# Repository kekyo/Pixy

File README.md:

# Pixy - Single board computer projects

Moved to [GitLab](https://gitlab.com/kekyo/Pixy).

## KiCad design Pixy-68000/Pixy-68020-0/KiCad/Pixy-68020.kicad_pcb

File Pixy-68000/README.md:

# Pixy-68000

## Specification

* [Motorola (NXP Freescale semiconductor) MC68SEC000-20](https://www.nxp.com/docs/en/product-brief/MC68SEC000.pdf) (Static low-powered m68k arch.)
* [ATMEL AVR ATMega-328PB](https://www.microchip.com/en-us/product/atmega328p)
  * Co-processor for 7segLEDs, LEDs, switches and serial interface.
  * Can program Arduino-like with [MiniCore project](https://github.com/MCUdude/MiniCore)
  * It can also be used in "ATMega-328P".
* [LATTICE MachXO2 LCMXO2-640](https://www.latticesemi.com/products/fpgaandcpld/machxo2)
  * Bus controller, captured all signals from the CPU.
* SRAM 1MB (512kbit * 2)
* Flash PROM 1MB (512kbit * 2, PLCC)

## PCB (Pixy-68000-0)

## Schematic (Pixy-68000-0)

[Pixy-68000-0-sch (PDF)](Images/Pixy-68000-0-sch.pdf)

## Errata (Pixy-68000-0)

1. Will fail writing Arduino (MiniCore) bootloader at first time.
   Please make this connection in your hand instead of J2 `AVR_ISP` connector.
   Then write to use Arduino MiniCore firmware writer.
   Once the firmware is written, this quick-hack wiring is not required thereafter.

## TODO:

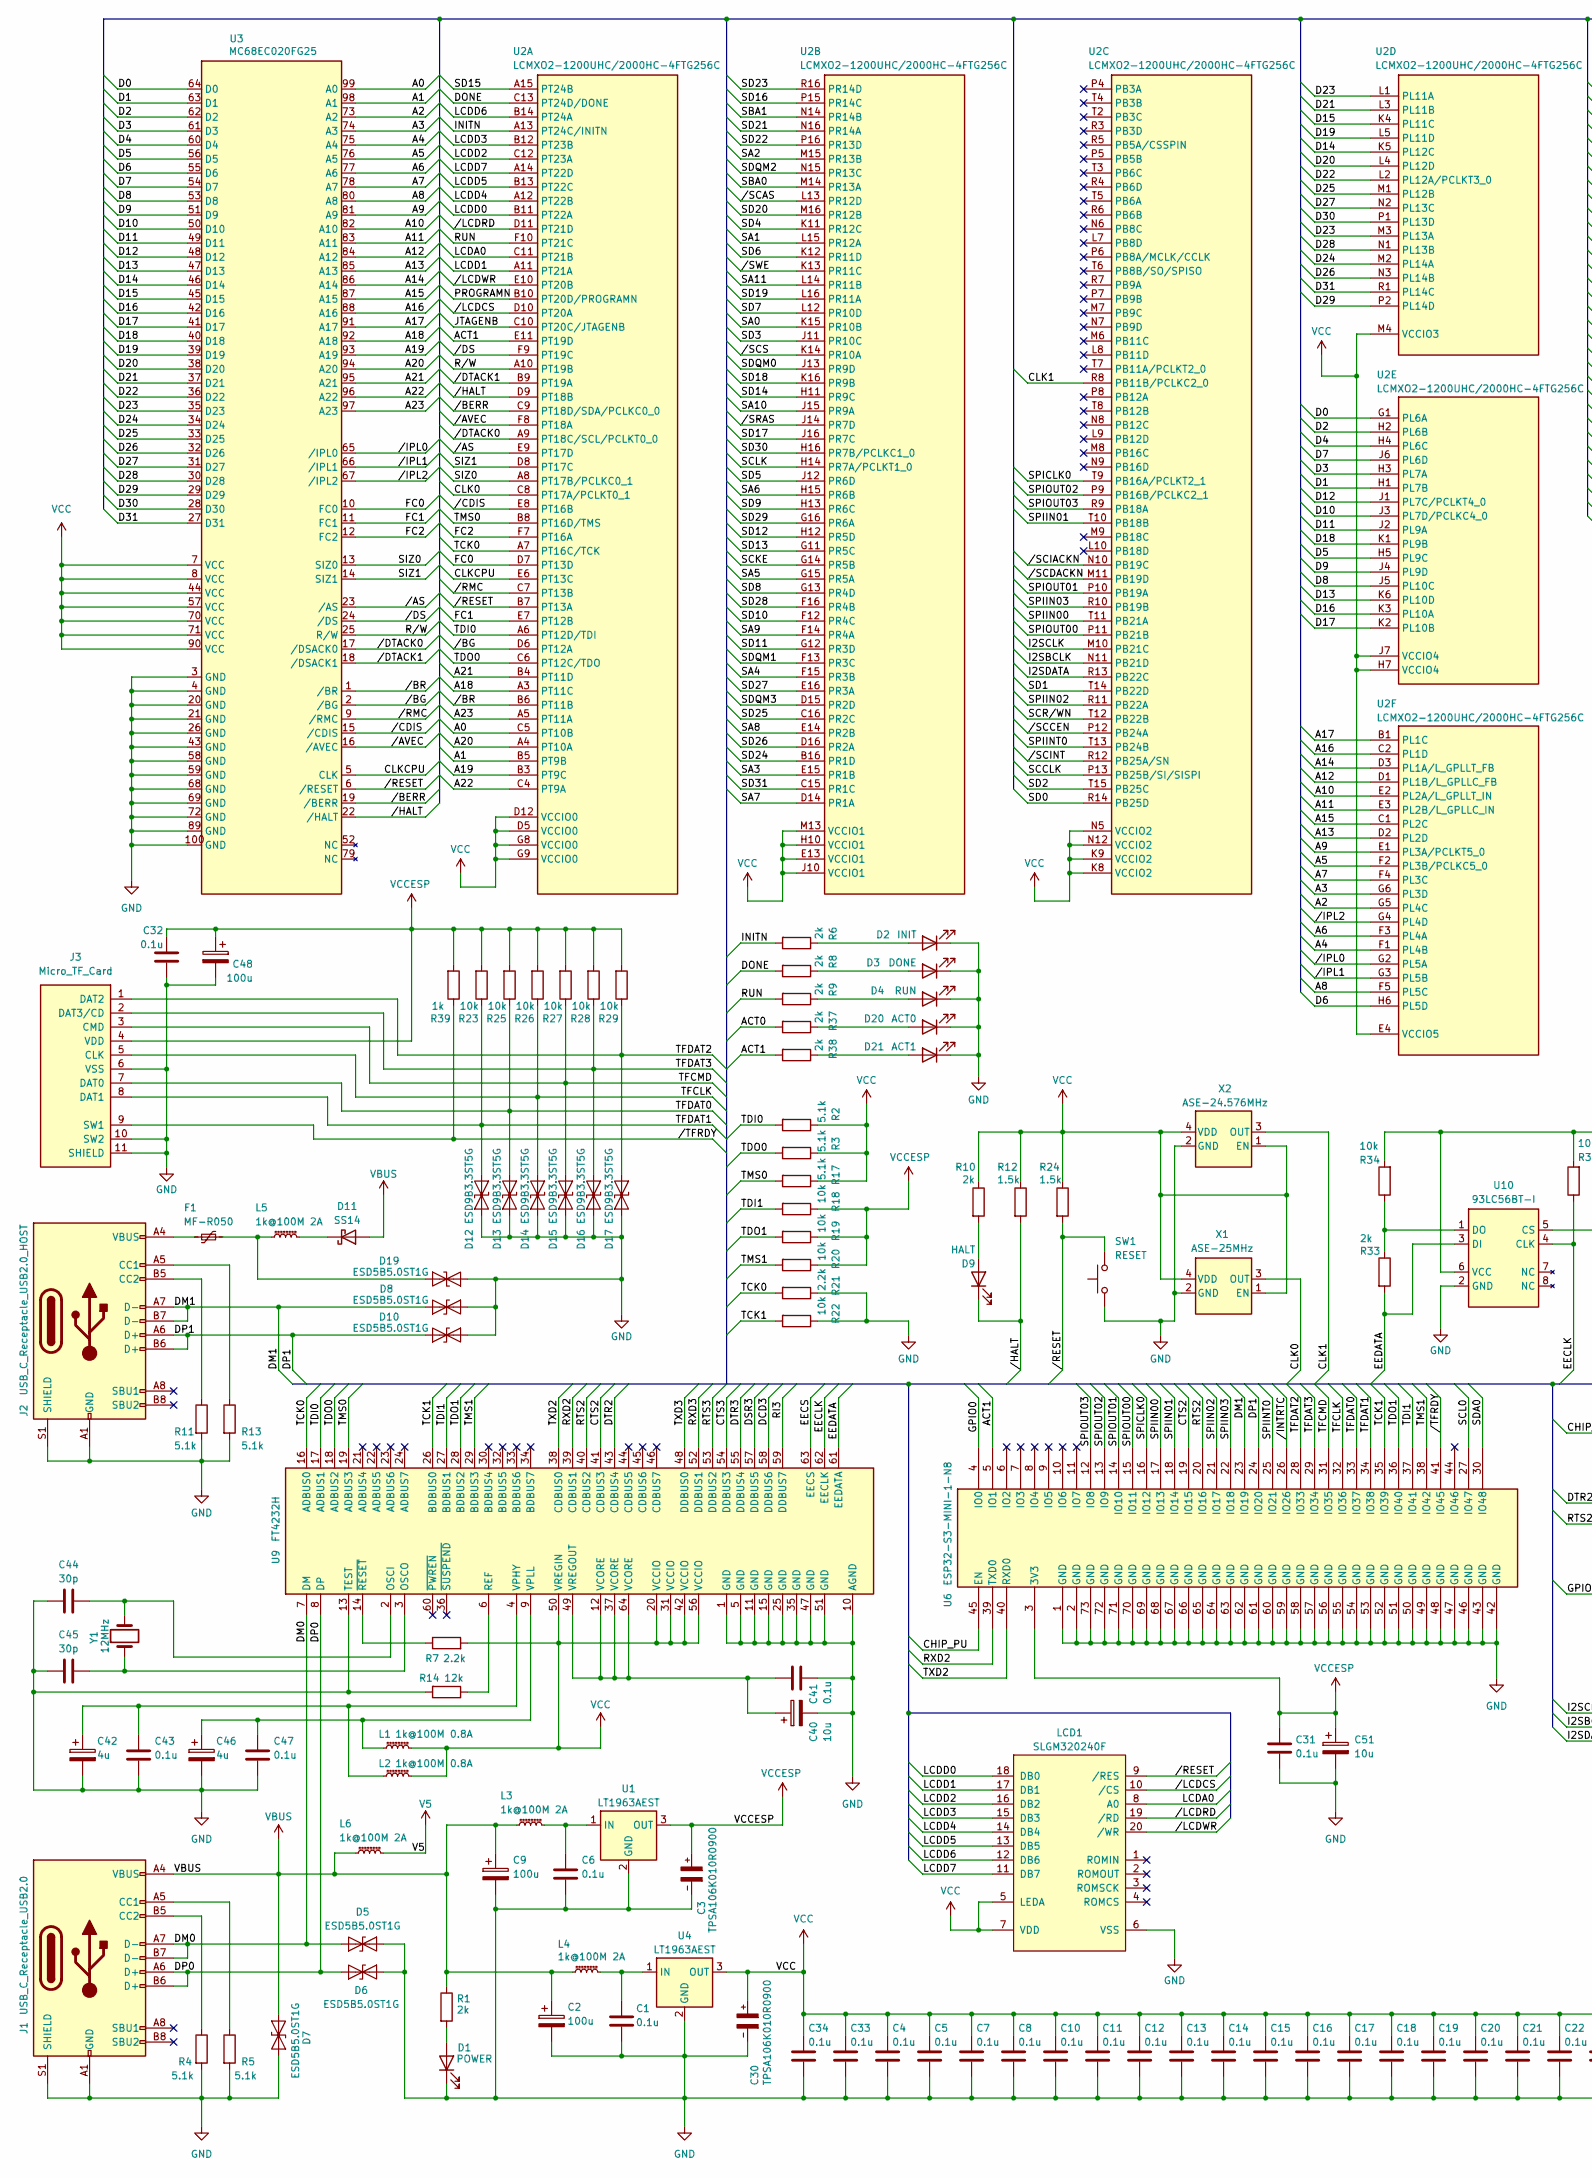
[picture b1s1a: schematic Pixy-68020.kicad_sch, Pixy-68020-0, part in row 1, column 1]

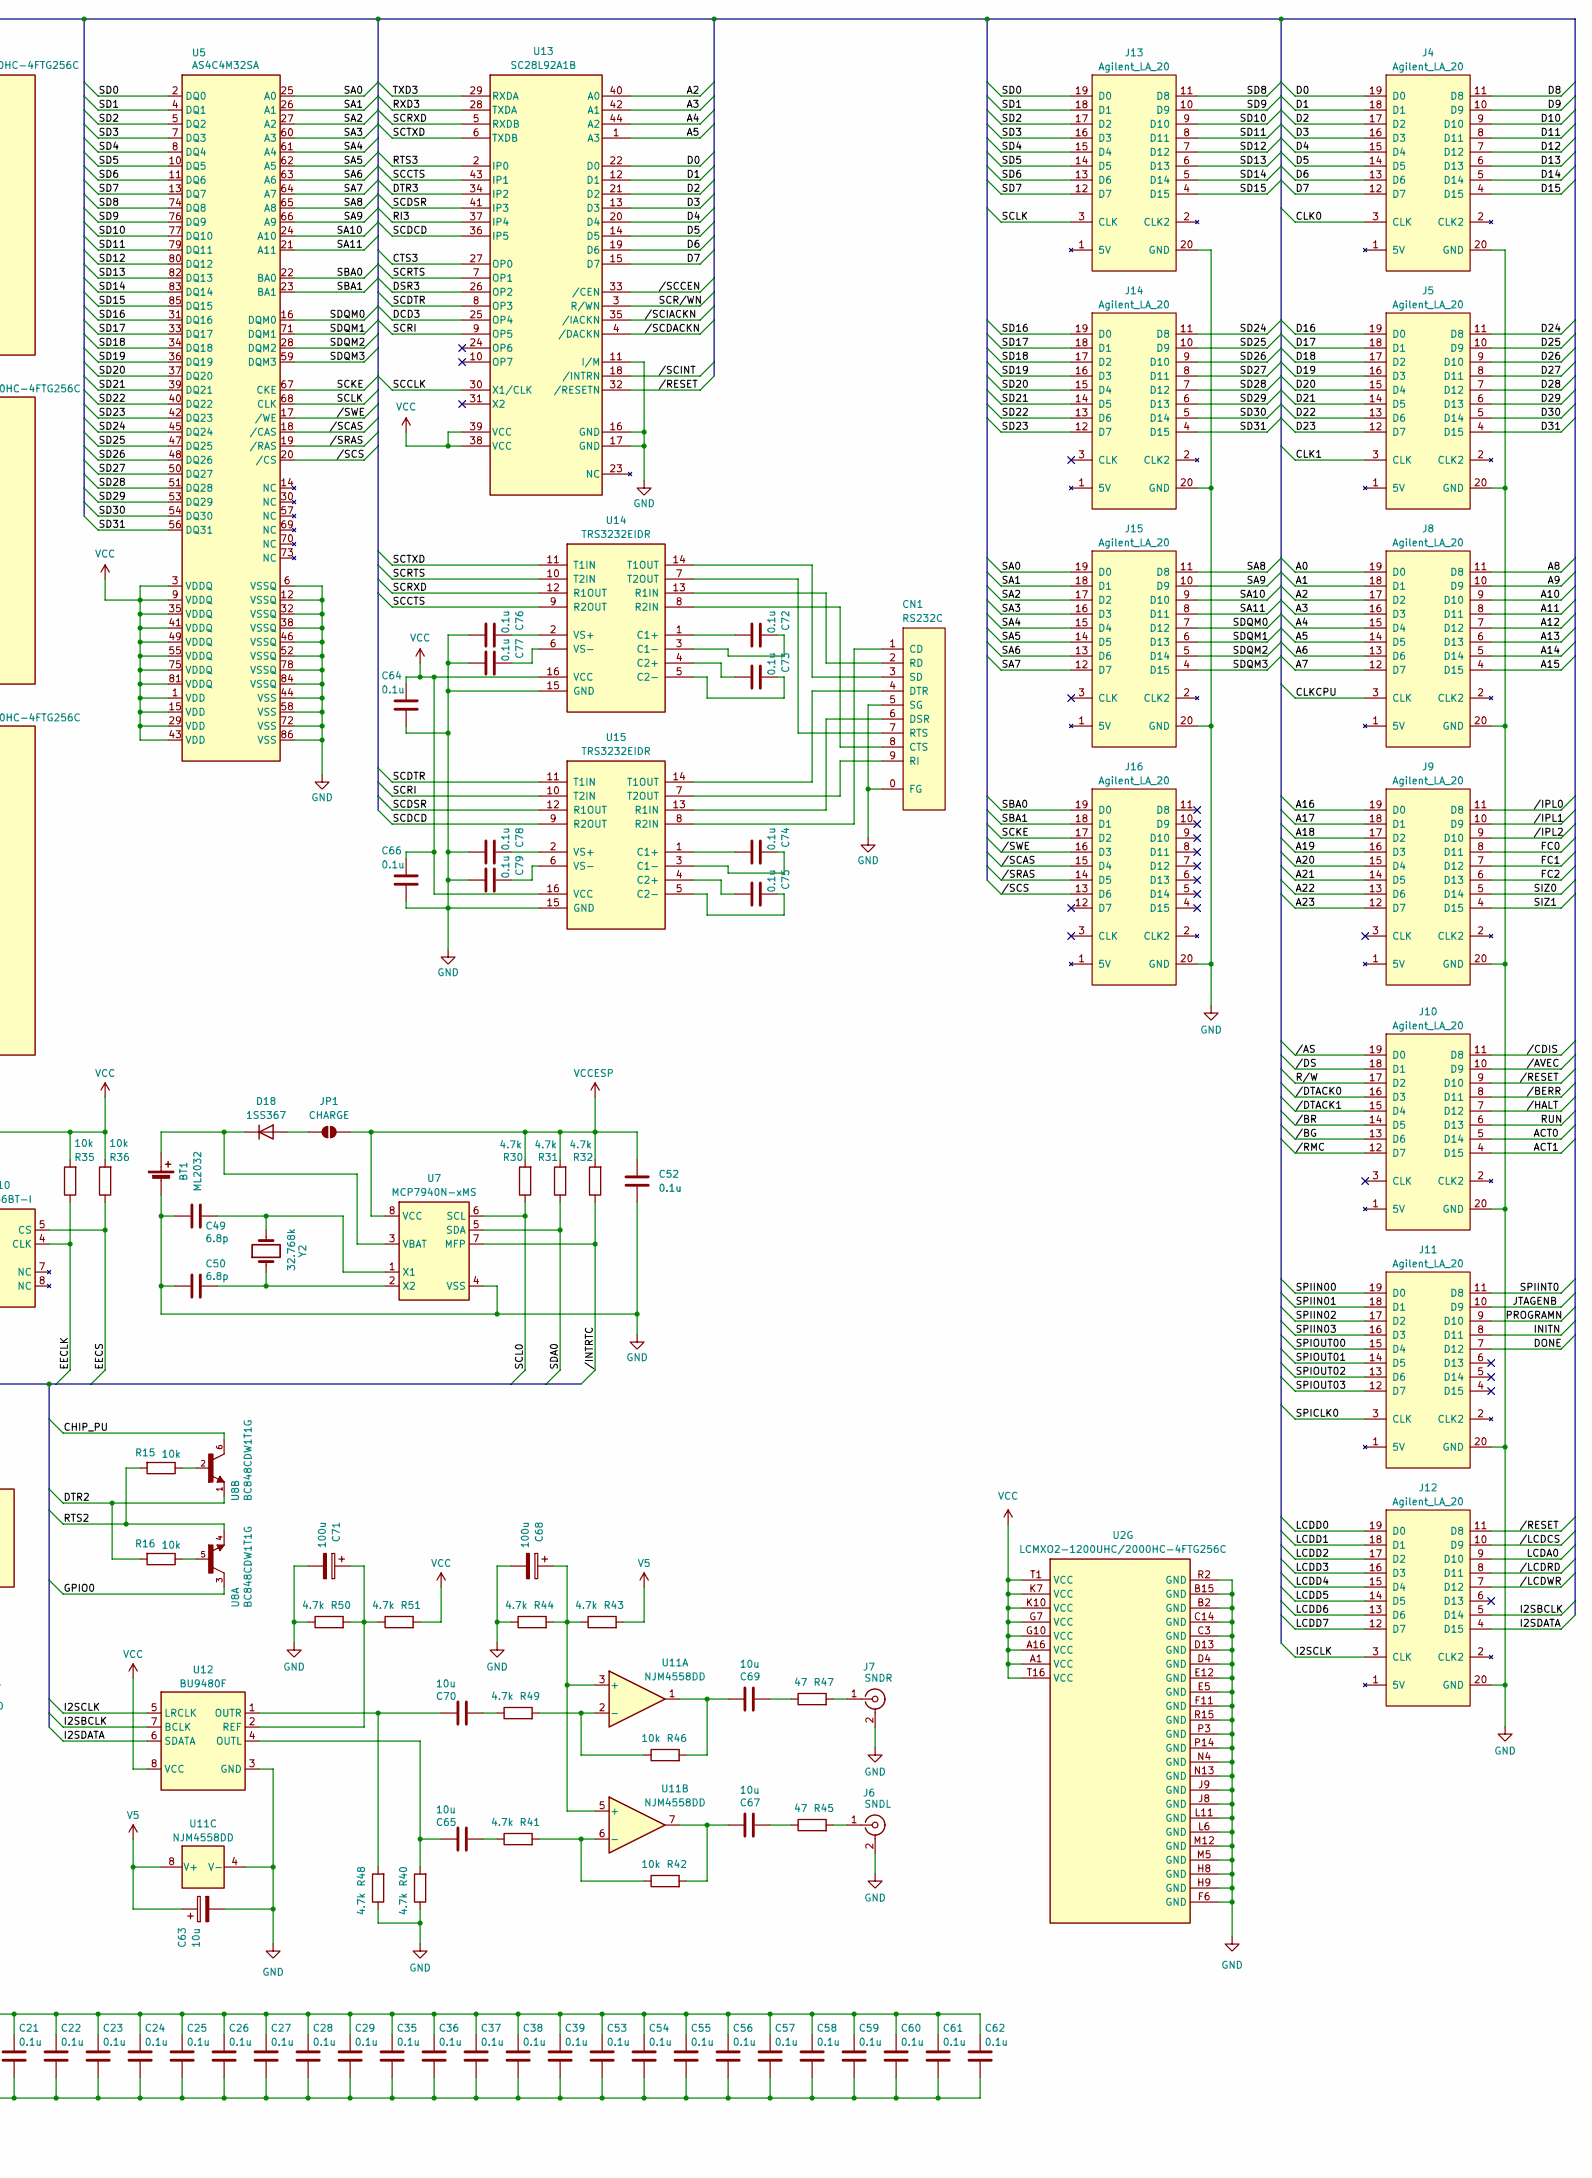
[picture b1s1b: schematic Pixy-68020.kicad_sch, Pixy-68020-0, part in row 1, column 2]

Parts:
BT1: ML2032; BatteryHolder_Keystone_103_1x20mm
C1, C4, C5, C6, C7, C8, C10, C11, C12, C13, C14, C15, C16, C17, C18, C19, C20, C21, C22, C23, C24, C25, C26, C27, C28, C29, C31, C32, C33, C34, C35, C36, C37, C38, C39, C41, C43, C47, C52, C53, C54, C55, C56, C57, C58, C59, C60, C61, C62, C64, C66, C72, C73, C74, C75, C76, C77, C78, C79: 0.1u; C_0805_2012
C2, C9, C48, C68, C71: 100u; CP_Radial_D5.0mm_P2.50mm
C3, C30: TPSA106K010R0900; CAPMP3216X166
C40, C51, C63: 10u; CP_Radial_D5.0mm_P2.50mm
C42, C46: 4u; CP_Radial_D5.0mm_P2.50mm
C44, C45: 30p; C_0805_2012
C49, C50: 6.8p; C_0805_2012
C65, C67, C69, C70: 10u; C_0805_2012
CN1: RS232C; DSUB-9_Pins_Horizontal_P2.77x2.84mm_EdgePinOffset4.94mm_Hou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
D1: POWER; LED_D3.0mm
D2: INIT; LED_D3.0mm
D3: DONE; LED_D3.0mm
D4: RUN; LED_D3.0mm
D5, D6, D7, D8, D10, D19: ESD5B5.0ST1G; D_SOD-523
D9: HALT; LED_D3.0mm
D11: SS14; D_SMA
D12, D13, D14, D15, D16, D17: ESD9B3.3ST5G; D_SOD-923
D18: 1SS367; D_SOD-323F
D20: ACT0; LED_D3.0mm
D21: ACT1; LED_D3.0mm
F1: MF-R050; Fuse_Bourns_MF-RG300
J1: USB_C_Receptacle_USB2.0; USB_C_Receptacle_HRO_TYPE-C-31-M-12
J2: USB_C_Receptacle_USB2.0_HOST; USB_C_Receptacle_HRO_TYPE-C-31-M-12
J3: Micro_TF_Card; Hirose_DM3D-SF
J4, J5, J8, J9, J10, J11, J12, J13, J14, J15, J16: Agilent_LA_20; PinHeader_2x10_P2.54mm_Vertical
J6: SNDL; CUI_RCJ-042
J7: SNDR; CUI_RCJ-042
JP1: CHARGE; SolderJumper-2_P1.3mm_Open_RoundedPad1.0x1.5mm
L1, L2: 1k@100M 0.8A; L_0603_1608
L3, L4, L5, L6: 1k@100M 2A; L_1206_3216
LCD1: SLGM320240F; PinHeader_1x20_P2.54mm_Vertical
R1, R6, R8, R9, R10, R33, R37, R38: 2k; R_0805_2012
R2, R3, R4, R5, R11, R13, R17: 5.1k; R_0805_2012
R7, R21: 2.2k; R_0805_2012
R12, R24: 1.5k; R_0805_2012
R14: 12k; R_0805_2012
R15, R16, R18, R19, R20, R22, R23, R25, R26, R27, R28, R29, R34, R35, R36, R42, R46: 10k; R_0805_2012
R30, R31, R32, R40, R41, R43, R44, R48, R49, R50, R51: 4.7k; R_0805_2012
R39: 1k; R_0805_2012
R45, R47: 47; R_0805_2012
SW1: RESET; TactSwitch
U1, U4: LT1963AEST; SOT-223-3_TabPin2
U2: LCMXO2-1200UHC/2000HC-4FTG256C; LCMXO2-FTG256
U3: MC68EC020FG25
U5: AS4C4M32SA; SOIC-86
U6: ESP32-S3-MINI-1-N8; ESP32-S3-MINI-1_EXP
U7: MCP7940N-xMS; MSOP-8_3x3mm_P0.65mm
U8: BC848CDW1T1G; SOT65P210X110-6N
U9: FT4232H; LQFP-64_10x10mm_P0.5mm
U10: 93LC56BT-I; MSOP-8_3x3mm_P0.65mm
U11: NJM4558DD; DIP-8_W7.62mm
U12: BU9480F; SOP-8_3.9x4.9mm_P1.27mm
U13: SC28L92A1B; SOT307-2_NXP-M
U14, U15: TRS3232EIDR; SOIC-16_3.9x9.9mm_P1.27mm
X1: ASE-25MHz; Oscillator_SMD_Abracon_ASE-4Pin_3.2x2.5mm_HandSoldering
X2: ASE-24.576MHz; Oscillator_SMD_Abracon_ASE-4Pin_3.2x2.5mm_HandSoldering
Y1: 12MHz; Crystal_HC18-U_Vertical
Y2: 32.768k; Crystal_HC18-U_Vertical

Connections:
/A0: J8.19 (D0), U2.C5 (PT10B), U3.99 (A0)
/A1: J8.18 (D1), U2.B5 (PT9B), U3.98 (A1)
/A2: J8.17 (D2), U2.G5 (PL4C), U3.73 (A2), U13.40 (A0)
/A3: J8.16 (D3), U2.G6 (PL3D), U3.74 (A3), U13.42 (A1)
/A4: J8.15 (D4), U2.F1 (PL4B), U3.75 (A4), U13.44 (A2)
/A5: J8.14 (D5), U2.F2 (PL3B/PCLKC5_0), U3.76 (A5), U13.1 (A3)
/A6: J8.13 (D6), U2.F3 (PL4A), U3.77 (A6)
/A7: J8.12 (D7), U2.F4 (PL3C), U3.78 (A7)
/A8: J8.11 (D8), U2.F5 (PL5C), U3.80 (A8)
/A9: J8.10 (D9), U2.E1 (PL3A/PCLKT5_0), U3.81 (A9)
/A10: J8.9 (D10), U2.E2 (PL2A/L_GPLLT_IN), U3.82 (A10)
/A11: J8.8 (D11), U2.E3 (PL2B/L_GPLLC_IN), U3.83 (A11)
/A12: J8.7 (D12), U2.D1 (PL1B/L_GPLLC_FB), U3.84 (A12)
/A13: J8.6 (D13), U2.D2 (PL2D), U3.85 (A13)
/A14: J8.5 (D14), U2.D3 (PL1A/L_GPLLT_FB), U3.86 (A14)
/A15: J8.4 (D15), U2.C1 (PL2C), U3.87 (A15)
/A16: J9.19 (D0), U2.C2 (PL1D), U3.88 (A16)
/A17: J9.18 (D1), U2.B1 (PL1C), U3.91 (A17)
/A18: J9.17 (D2), U2.A3 (PT11C), U3.92 (A18)
/A19: J9.16 (D3), U2.B3 (PT9C), U3.93 (A19)
/A20: J9.15 (D4), U2.A4 (PT10A), U3.94 (A20)
/A21: J9.14 (D5), U2.B4 (PT11D), U3.95 (A21)
/A22: J9.13 (D6), U2.C4 (PT9A), U3.96 (A22)
/A23: J9.12 (D7), U2.A5 (PT11A), U3.97 (A23)
/ACT0: J10.5 (D14), R37.2
/ACT1: J10.4 (D15), R38.2, U2.E11 (PT19D), U6.5 (IO1)
/CHIP_PU: U6.45 (EN), U8.6
/CLK0: J4.3 (CLK), U2.C8 (PT17A/PCLKT0_1), X1.3 (OUT)
/CLK1: J5.3 (CLK), U2.R8 (PB11B/PCLKC2_0), X2.3 (OUT)
/CLKCPU: J8.3 (CLK), U2.E6 (PT13C), U3.5 (CLK)
/CTS2: U6.19 (IO15), U9.41 (CDBUS3)
/CTS3: U9.54 (DDBUS3), U13.27 (OP0)
/D0: J4.19 (D0), U2.G1 (PL6A), U3.64 (D0), U13.22 (D0)
/D1: J4.18 (D1), U2.H1 (PL7B), U3.63 (D1), U13.12 (D1)
/D2: J4.17 (D2), U2.H2 (PL6B), U3.62 (D2), U13.21 (D2)
/D3: J4.16 (D3), U2.H3 (PL7A), U3.61 (D3), U13.13 (D3)
/D4: J4.15 (D4), U2.H4 (PL6C), U3.60 (D4), U13.20 (D4)
/D5: J4.14 (D5), U2.H5 (PL9C), U3.56 (D5), U13.14 (D5)
/D6: J4.13 (D6), U2.H6 (PL5D), U3.55 (D6), U13.19 (D6)
/D7: J4.12 (D7), U2.J6 (PL6D), U3.54 (D7), U13.15 (D7)
/D8: J4.11 (D8), U2.J5 (PL10C), U3.53 (D8)
/D9: J4.10 (D9), U2.J4 (PL9D), U3.51 (D9)
/D10: J4.9 (D10), U2.J3 (PL7D/PCLKC4_0), U3.50 (D10)
/D11: J4.8 (D11), U2.J2 (PL9A), U3.49 (D11)
/D12: J4.7 (D12), U2.J1 (PL7C/PCLKT4_0), U3.48 (D12)
/D13: J4.6 (D13), U2.K6 (PL10D), U3.47 (D13)
/D14: J4.5 (D14), U2.K5 (PL12C), U3.46 (D14)
/D15: J4.4 (D15), U2.K4 (PL11C), U3.45 (D15)
/D16: J5.19 (D0), U2.K3 (PL10A), U3.42 (D16)
/D17: J5.18 (D1), U2.K2 (PL10B), U3.41 (D17)
/D18: J5.17 (D2), U2.K1 (PL9B), U3.40 (D18)
/D19: J5.16 (D3), U2.L5 (PL11D), U3.39 (D19)
/D20: J5.15 (D4), U2.L4 (PL12D), U3.38 (D20)
/D21: J5.14 (D5), U2.L3 (PL11B), U3.37 (D21)
/D22: J5.13 (D6), U2.L2 (PL12A/PCLKT3_0), U3.36 (D22)
/D23: J5.12 (D7), U2.L1 (PL11A), U2.M3 (PL13A), U3.35 (D23)
/D24: J5.11 (D8), U2.M2 (PL14A), U3.34 (D24)
/D25: J5.10 (D9), U2.M1 (PL12B), U3.33 (D25)
/D26: J5.9 (D10), U2.N3 (PL14B), U3.32 (D26)
/D27: J5.8 (D11), U2.N2 (PL13C), U3.31 (D27)
/D28: J5.7 (D12), U2.N1 (PL13B), U3.30 (D28)
/D29: J5.6 (D13), U2.P2 (PL14D), U3.29 (D29)
/D30: J5.5 (D14), U2.P1 (PL13D), U3.28 (D30)
/D31: J5.4 (D15), U2.R1 (PL14C), U3.27 (D31)
/DCD3: U9.58 (DDBUS6), U13.25 (OP4)
/DM0: D5.1 (A1), J1.A7 (D-), J1.B7 (D-), U9.7 (DM)
/DM1: D8.1 (A1), J2.A7 (D-), J2.B7 (D-), U6.23 (IO19)
/DONE: J11.7 (D12), R8.2, U2.C13 (PT24D/DONE)
/DP0: D6.1 (A1), J1.A6 (D+), J1.B6 (D+), U9.8 (DP)
/DP1: D10.1 (A1), J2.A6 (D+), J2.B6 (D+), U6.24 (IO20)
/DSR3: U9.57 (DDBUS5), U13.26 (OP2)
/DTR2: R16.2, U8.1, U9.43 (CDBUS4)
/DTR3: U9.55 (DDBUS4), U13.34 (IP2)
/EECLK: R35.1, U9.62 (EECLK), U10.4 (CLK)
/EECS: R36.1, U9.63 (EECS), U10.5 (CS)
/EEDATA: R33.2, U9.61 (EEDATA), U10.3 (DI)
/FC0: J9.8 (D11), U2.D7 (PT13D), U3.10 (FC0)
/FC1: J9.7 (D12), U2.E7 (PT12B), U3.11 (FC1)
/FC2: J9.6 (D13), U2.F7 (PT16A), U3.12 (FC2)
/GPIO0: U6.4 (IO0), U8.3
/I2SBCLK: J12.5 (D14), U2.N11 (PB21D), U12.7 (BCLK)
/I2SCLK: J12.3 (CLK), U2.M10 (PB21C), U12.5 (LRCLK)
/I2SDATA: J12.4 (D15), U2.R13 (PB22C), U12.6 (SDATA)
/INITN: J11.8 (D11), R6.2, U2.A13 (PT24C/INITN)
/JTAGENB: J11.10 (D9), U2.C10 (PT20C/JTAGENB)
/LCDA0: J12.9 (D10), LCD1.8 (A0), U2.C11 (PT21B)
/LCDD0: J12.19 (D0), LCD1.18 (DB0), U2.B11 (PT22A)
/LCDD1: J12.18 (D1), LCD1.17 (DB1), U2.A11 (PT21A)
/LCDD2: J12.17 (D2), LCD1.16 (DB2), U2.C12 (PT23A)
/LCDD3: J12.16 (D3), LCD1.15 (DB3), U2.B12 (PT23B)
/LCDD4: J12.15 (D4), LCD1.14 (DB4), U2.A12 (PT22B)
/LCDD5: J12.14 (D5), LCD1.13 (DB5), U2.B13 (PT22C)
/LCDD6: J12.13 (D6), LCD1.12 (DB6), U2.B14 (PT24A)
/LCDD7: J12.12 (D7), LCD1.11 (DB7), U2.A14 (PT22D)
/RI3: U9.59 (DDBUS7), U13.37 (IP4)
/RTS2: R15.2, U6.20 (IO16), U8.4, U9.40 (CDBUS2)
/RTS3: U9.53 (DDBUS2), U13.2 (IP0)
/RUN: J10.6 (D13), R9.2, U2.F10 (PT21C)
/RXD2: U6.39 (TXD0), U9.39 (CDBUS1)
/RXD3: U9.52 (DDBUS1), U13.28 (TXDA)
/R/W: J10.17 (D2), U2.A10 (PT19B), U3.25 (R/W)
/SA0: J15.19 (D0), U2.K15 (PR10B), U5.25 (A0)
/SA1: J15.18 (D1), U2.L15 (PR12A), U5.26 (A1)
/SA2: J15.17 (D2), U2.M15 (PR13B), U5.27 (A2)
/SA3: J15.16 (D3), U2.E15 (PR1B), U5.60 (A3)
/SA4: J15.15 (D4), U2.F15 (PR3B), U5.61 (A4)
/SA5: J15.14 (D5), U2.G15 (PR5A), U5.62 (A5)
/SA6: J15.13 (D6), U2.H15 (PR6B), U5.63 (A6)
/SA7: J15.12 (D7), U2.D14 (PR1A), U5.64 (A7)
/SA8: J15.11 (D8), U2.E14 (PR2B), U5.65 (A8)
/SA9: J15.10 (D9), U2.F14 (PR4A), U5.66 (A9)
/SA10: J15.9 (D10), U2.J15 (PR9A), U5.24 (A10)
/SA11: J15.8 (D11), U2.L14 (PR11B), U5.21 (A11)
/SBA0: J16.19 (D0), U2.M14 (PR13A), U5.22 (BA0)
/SBA1: J16.18 (D1), U2.N14 (PR14B), U5.23 (BA1)
/SCCLK: U2.P13 (PB25B/SI/SISPI), U13.30 (X1/CLK)
/SCCTS: U13.43 (IP1), U14.9 (R2OUT)
/SCDCD: U13.36 (IP5), U15.9 (R2OUT)
/SCDSR: U13.41 (IP3), U15.12 (R1OUT)
/SCDTR: U13.8 (OP3), U15.11 (T1IN)
/SCKE: J16.17 (D2), U2.G14 (PR5B), U5.67 (CKE)
/SCL0: R30.1, U6.27 (IO47), U7.6 (SCL)
/SCLK: J13.3 (CLK), U2.H14 (PR7A/PCLKT1_0), U5.68 (CLK)
/SCRI: U13.9 (OP5), U15.10 (T2IN)
/SCRTS: U13.7 (OP1), U14.10 (T2IN)
/SCRXD: U13.5 (RXDB), U14.12 (R1OUT)
/SCR/WN: U2.T12 (PB22B), U13.3 (R/WN)
/SCTXD: U13.6 (TXDB), U14.11 (T1IN)
/SD0: J13.19 (D0), U2.R14 (PB25D), U5.2 (DQ0)
/SD1: J13.18 (D1), U2.T14 (PB22D), U5.4 (DQ1)
/SD2: J13.17 (D2), U2.T15 (PB25C), U5.5 (DQ2)
/SD3: J13.16 (D3), U2.J11 (PR10C), U5.7 (DQ3)
/SD4: J13.15 (D4), U2.K11 (PR12C), U5.8 (DQ4)
/SD5: J13.14 (D5), U2.J12 (PR6D), U5.10 (DQ5)
/SD6: J13.13 (D6), U2.K12 (PR11D), U5.11 (DQ6)
/SD7: J13.12 (D7), U2.L12 (PR10D), U5.13 (DQ7)
/SD8: J13.11 (D8), U2.G13 (PR4D), U5.74 (DQ8)
/SD9: J13.10 (D9), U2.H13 (PR6C), U5.76 (DQ9)
/SD10: J13.9 (D10), U2.F12 (PR4C), U5.77 (DQ10)
/SD11: J13.8 (D11), U2.G12 (PR3D), U5.79 (DQ11)
/SD12: J13.7 (D12), U2.H12 (PR5D), U5.80 (DQ12)
/SD13: J13.6 (D13), U2.G11 (PR5C), U5.82 (DQ13)
/SD14: J13.5 (D14), U2.H11 (PR9C), U5.83 (DQ14)
/SD15: J13.4 (D15), U2.A15 (PT24B), U5.85 (DQ15)
/SD16: J14.19 (D0), U2.P15 (PR14C), U5.31 (DQ16)
/SD17: J14.18 (D1), U2.J16 (PR7C), U5.33 (DQ17)
/SD18: J14.17 (D2), U2.K16 (PR9B), U5.34 (DQ18)
/SD19: J14.16 (D3), U2.L16 (PR11A), U5.36 (DQ19)
/SD20: J14.15 (D4), U2.M16 (PR12B), U5.37 (DQ20)
/SD21: J14.14 (D5), U2.N16 (PR14A), U5.39 (DQ21)
/SD22: J14.13 (D6), U2.P16 (PR13D), U5.40 (DQ22)
/SD23: J14.12 (D7), U2.R16 (PR14D), U5.42 (DQ23)
/SD24: J14.11 (D8), U2.B16 (PR1D), U5.45 (DQ24)
/SD25: J14.10 (D9), U2.C16 (PR2C), U5.47 (DQ25)
/SD26: J14.9 (D10), U2.D16 (PR2A), U5.48 (DQ26)
/SD27: J14.8 (D11), U2.E16 (PR3A), U5.50 (DQ27)
/SD28: J14.7 (D12), U2.F16 (PR4B), U5.51 (DQ28)
/SD29: J14.6 (D13), U2.G16 (PR6A), U5.53 (DQ29)
/SD30: J14.5 (D14), U2.H16 (PR7B/PCLKC1_0), U5.54 (DQ30)
/SD31: J14.4 (D15), U2.C15 (PR1C), U5.56 (DQ31)
/SDA0: R31.1, U6.30 (IO48), U7.5 (SDA)
/SDQM0: J15.7 (D12), U2.J13 (PR9D), U5.16 (DQM0)
/SDQM1: J15.6 (D13), U2.F13 (PR3C), U5.71 (DQM1)
/SDQM2: J15.5 (D14), U2.N15 (PR13C), U5.28 (DQM2)
/SDQM3: J15.4 (D15), U2.D15 (PR2D), U5.59 (DQM3)
/SIZ0: J9.5 (D14), U2.A8 (PT17B/PCLKC0_1), U3.13 (SIZ0)
/SIZ1: J9.4 (D15), U2.D8 (PT17C), U3.14 (SIZ1)
/SPICLK0: J11.3 (CLK), U2.T9 (PB16A/PCLKT2_1), U6.16 (IO12)
/SPIIN00: J11.19 (D0), U2.T11 (PB21A), U6.17 (IO13)
/SPIIN01: J11.18 (D1), U2.T10 (PB18B), U6.18 (IO14)
/SPIIN02: J11.17 (D2), U2.R11 (PB22A), U6.21 (IO17)
/SPIIN03: J11.16 (D3), U2.R10 (PB19B), U6.22 (IO18)
/SPIINT0: J11.11 (D8), U2.T13 (PB24B), U6.25 (IO21)
/SPIOUT00: J11.15 (D4), U2.P11 (PB21B), U6.15 (IO11)
/SPIOUT01: J11.14 (D5), U2.P10 (PB19A), U6.14 (IO10)
/SPIOUT02: J11.13 (D6), U2.P9 (PB16B/PCLKC2_1), U6.13 (IO9)
/SPIOUT03: J11.12 (D7), U2.R9 (PB18A), U6.12 (IO8)
/TCK0: R21.2, U2.A7 (PT16C/TCK), U9.16 (ADBUS0)
/TCK1: R22.2, U6.35 (IO39), U9.26 (BDBUS0)
/TDI0: R2.2, U2.A6 (PT12D/TDI), U9.17 (ADBUS1)
/TDI1: R18.2, U6.37 (IO41), U9.27 (BDBUS1)
/TDO0: R3.2, U2.C6 (PT12C/TDO), U9.18 (ADBUS2)
/TDO1: R19.2, U6.36 (IO40), U9.28 (BDBUS2)
/TFCLK: D14.1 (A1), J3.5 (CLK), R26.1, U6.32 (IO36)
/TFCMD: D15.1 (A1), J3.3 (CMD), R27.1, U6.31 (IO35)
/TFDAT0: D13.1 (A1), J3.7 (DAT0), R25.1, U6.33 (IO37)
/TFDAT1: D12.1 (A1), J3.8 (DAT1), R23.1, U6.34 (IO38)
/TFDAT2: D17.1 (A1), J3.1 (DAT2), R29.1, U6.28 (IO33)
/TFDAT3: D16.1 (A1), J3.2 (DAT3/CD), R28.1, U6.29 (IO34)
/TMS0: R17.2, U2.B8 (PT16D/TMS), U9.19 (ADBUS3)
/TMS1: R20.2, U6.38 (IO42), U9.29 (BDBUS3)
/TXD2: U6.40 (RXD0), U9.38 (CDBUS0)
/TXD3: U9.48 (DDBUS0), U13.29 (RXDA)
//AS: J10.19 (D0), U2.E9 (PT17D), U3.23 (/AS)
//AVEC: J10.10 (D9), U2.F8 (PT18A), U3.16 (/AVEC)
//BERR: J10.8 (D11), U2.C9 (PT18D/SDA/PCLKC0_0), U3.19 (/BERR)
//BG: J10.13 (D6), U2.D6 (PT12A), U3.2 (/BG)
//BR: J10.14 (D5), U2.B6 (PT11B), U3.1 (/BR)
//CDIS: J10.11 (D8), U2.E8 (PT16B), U3.15 (/CDIS)
//DS: J10.18 (D1), U2.F9 (PT19C), U3.24 (/DS)
//DTACK0: J10.16 (D3), U2.A9 (PT18C/SCL/PCLKT0_0), U3.17 (/DSACK0)
//DTACK1: J10.15 (D4), U2.B9 (PT19A), U3.18 (/DSACK1)
//HALT: D9.1 (K), J10.7 (D12), R12.2, U2.D9 (PT18B), U3.22 (/HALT)
//INTRTC: R32.1, U6.26 (IO26), U7.7 (MFP)
//IPL0: J9.11 (D8), U2.G2 (PL5A), U3.65 (/IPL0)
//IPL1: J9.10 (D9), U2.G3 (PL5B), U3.66 (/IPL1)
//IPL2: J9.9 (D10), U2.G4 (PL4D), U3.67 (/IPL2)
//LCDCS: J12.10 (D9), LCD1.10 (/CS), U2.D10 (PT20A)
//LCDRD: J12.8 (D11), LCD1.19 (/RD), U2.D11 (PT21D)
//LCDWR: J12.7 (D12), LCD1.20 (/WR), U2.E10 (PT20B)
//RESET: J10.9 (D10), J12.11 (D8), LCD1.9 (/RES), R24.2, SW1.2, U2.B7 (PT13A), U3.6 (/RESET), U13.32 (/RESETN)
//RMC: J10.12 (D7), U2.C7 (PT13B), U3.9 (/RMC)
//SCAS: J16.15 (D4), U2.L13 (PR12D), U5.18 (/CAS)
//SCCEN: U2.P12 (PB24A), U13.33 (/CEN)
//SCDACKN: U2.M11 (PB19D), U13.4 (/DACKN)
//SCIACKN: U2.N10 (PB19C), U13.35 (/IACKN)
//SCINT: U2.R12 (PB25A/SN), U13.18 (/INTRN)
//SCS: J16.13 (D6), U2.K14 (PR10A), U5.20 (/CS)
//SRAS: J16.14 (D5), U2.J14 (PR7D), U5.19 (/RAS)
//SWE: J16.16 (D3), U2.K13 (PR11C), U5.17 (/WE)
//TFRDY: J3.9 (SW1), R39.1, U6.41 (IO45)
GND: BT1.2 (-), C1.2, C2.2, C3.-, C4.2, C5.2, C6.2, C7.2, C8.2, C9.2, C10.2, C11.2, C12.2, C13.2, C14.2, C15.2, C16.2, C17.2, C18.2, C19.2, C20.2, C21.2, C22.2, C23.2, C24.2, C25.2, C26.2, C27.2, C28.2, C29.2, C30.-, C31.2, C32.2, C33.2, C34.2, C35.2, C36.2, C37.2, C38.2, C39.2, C40.2, C41.2, C42.2, C43.2, C44.2, C45.2, C46.2, C47.2, C48.2, C49.2, C50.2, C51.2, C52.2, C53.2, C54.2, C55.2, C56.2, C57.2, C58.2, C59.2, C60.2, C61.2, C62.2, C63.2, C64.2, C66.2, C68.2, C71.2, C76.2, C77.2, C78.2, C79.2, CN1.0 (FG), CN1.5 (SG), D1.1 (K), D2.1 (K), D3.1 (K), D4.1 (K), D5.2 (A2), D6.2 (A2), D7.2 (A2), D8.2 (A2), D10.2 (A2), D12.2 (A2), D13.2 (A2), D14.2 (A2), D15.2 (A2), D16.2 (A2), D17.2 (A2), D19.1 (A1), D20.1 (K), D21.1 (K), J1.A1 (GND), J1.A12 (GND), J1.B1 (GND), J1.B12 (GND), J1.S1 (SHIELD), J2.A1 (GND), J2.A12 (GND), J2.B1 (GND), J2.B12 (GND), J2.S1 (SHIELD), J3.6 (VSS), J3.10 (SW2), J3.11 (SHIELD), J4.20 (GND), J5.20 (GND), J6.2 (Ext), J7.2 (Ext), J8.20 (GND), J9.20 (GND), J10.20 (GND), J11.9 (D10), J11.20 (GND), J12.20 (GND), J13.20 (GND), J14.20 (GND), J15.20 (GND), J16.20 (GND), LCD1.6 (VSS), R4.2, R5.2, R11.2, R13.2, R14.2, R21.1, R22.1, R40.1, R44.1, R48.1, R50.1, SW1.1, U1.2 (GND), U2.B2 (GND), U2.B10 (PT20D/PROGRAMN), U2.B15 (GND), U2.C3 (GND), U2.C14 (GND), U2.D4 (GND), U2.D13 (GND), U2.E5 (GND), U2.E12 (GND), U2.F6 (GND), U2.F11 (GND), U2.H8 (GND), U2.H9 (GND), U2.J8 (GND), U2.J9 (GND), U2.L6 (GND), U2.L11 (GND), U2.M5 (GND), U2.M12 (GND), U2.N4 (GND), U2.N13 (GND), U2.P3 (GND), U2.P14 (GND), U2.R2 (GND), U2.R15 (GND), U3.3 (GND), U3.4 (GND), U3.20 (GND), U3.21 (GND), U3.26 (GND), U3.43 (GND), U3.58 (GND), U3.59 (GND), U3.68 (GND), U3.69 (GND), U3.72 (GND), U3.89 (GND), U3.100 (GND), U4.2 (GND), U5.6 (VSSQ), U5.12 (VSSQ), U5.32 (VSSQ), U5.38 (VSSQ), U5.44 (VSS), U5.46 (VSSQ), U5.52 (VSSQ), U5.58 (VSS), U5.72 (VSS), U5.78 (VSSQ), U5.84 (VSSQ), U5.86 (VSS), U6.1 (GND), U6.2 (GND), U6.42 (GND), U6.43 (GND), U6.46 (GND), U6.47 (GND), U6.48 (GND), U6.49 (GND), U6.50 (GND), U6.51 (GND), U6.52 (GND), U6.53 (GND), U6.54 (GND), U6.55 (GND), U6.56 (GND), U6.57 (GND), U6.58 (GND), U6.59 (GND), U6.60 (GND), U6.61 (GND), U6.62 (GND), U6.63 (GND), U6.64 (GND), U6.65 (GND), U6.66 (GND), U6.67 (GND), U6.68 (GND), U6.69 (GND), U6.70 (GND), U6.71 (GND), U6.72 (GND), U6.73 (GND), U7.4 (VSS), U9.1 (GND), U9.5 (GND), U9.10 (AGND), U9.11 (GND), U9.13 (TEST), U9.15 (GND), U9.25 (GND), U9.35 (GND), U9.47 (GND), U9.51 (GND), U10.2 (GND), U11.4 (V-), U12.3 (GND), U13.11 (I/M), U13.16 (GND), U13.17 (GND), U14.15 (GND), U15.15 (GND), X1.2 (GND), X2.2 (GND)
unnamed: BT1.1 (+), D18.1 (K), U7.3 (VBAT)
unnamed: C65.1, R41.1
unnamed: C67.1, R45.1
unnamed: C67.2, R42.2, U11.7
unnamed: C69.1, R47.1
unnamed: C69.2, R46.2, U11.1
unnamed: C70.1, R49.1
unnamed: CN1.1 (CD), U15.8 (R2IN)
unnamed: CN1.8 (CTS), U14.8 (R2IN)
unnamed: CN1.6 (DSR), U15.13 (R1IN)
unnamed: CN1.4 (DTR), U15.14 (T1OUT)
unnamed: CN1.2 (RD), U14.13 (R1IN)
unnamed: CN1.9 (RI), U15.7 (T2OUT)
unnamed: CN1.7 (RTS), U14.7 (T2OUT)
unnamed: CN1.3 (SD), U14.14 (T1OUT)
unnamed: D1.2 (A), R1.2
unnamed: D2.2 (A), R6.1
unnamed: D3.2 (A), R8.1
unnamed: D4.2 (A), R9.1
unnamed: D9.2 (A), R10.2
unnamed: D11.1 (K), L5.1
unnamed: D18.2 (A), JP1.1 (A)
unnamed: D19.2 (A2), F1.1, L5.2
unnamed: D20.2 (A), R37.1
unnamed: D21.2 (A), R38.1
unnamed: F1.2, J2.A4 (VBUS), J2.A9 (VBUS), J2.B4 (VBUS), J2.B9 (VBUS)
unnamed: J1.A5 (CC1), R5.1
unnamed: J1.B5 (CC2), R4.1
unnamed: J2.A5 (CC1), R13.1
unnamed: J2.B5 (CC2), R11.1
unnamed: J6.1 (In), R45.2
unnamed: J7.1 (In), R47.2
unnamed: R15.1, U8.2
unnamed: R16.1, U8.5
unnamed: C6.1, L3.1, U1.1 (IN)
unnamed: C1.1, L4.1, U4.1 (IN)
unnamed: C49.1, U7.1 (X1), Y2.2
unnamed: C50.1, U7.2 (X2), Y2.1
unnamed: C44.1, U9.2 (OSCI), Y1.2
unnamed: C45.1, U9.3 (OSCO), Y1.1
unnamed: R14.1, U9.6 (REF)
unnamed: C42.1, C43.1, L2.2, U9.4 (VPHY)
unnamed: C46.1, C47.1, L1.2, U9.9 (VPLL)
unnamed: C40.1, C41.1, U9.12 (VCORE), U9.37 (VCORE), U9.49 (VREGOUT), U9.64 (VCORE)
unnamed: R7.1, U9.14 (~RESET)
unnamed: R33.1, R34.1, U10.1 (DO)
unnamed: C68.1, R43.1, R44.2, U11.3 (+), U11.5 (+)
unnamed: R46.1, R49.2, U11.2 (-)
unnamed: R41.2, R42.1, U11.6 (-)
unnamed: C65.2, R40.2, U12.4 (OUTL)
unnamed: C70.2, R48.2, U12.1 (OUTR)
unnamed: C71.1, R50.2, R51.1, U12.2 (REF)
unnamed: C72.2, U14.1 (C1+)
unnamed: C72.1, U14.3 (C1-)
unnamed: C73.2, U14.4 (C2+)
unnamed: C73.1, U14.5 (C2-)
unnamed: C76.1, U14.2 (VS+)
unnamed: C77.1, U14.6 (VS-)
unnamed: C74.2, U15.1 (C1+)
unnamed: C74.1, U15.3 (C1-)
unnamed: C75.2, U15.4 (C2+)
unnamed: C75.1, U15.5 (C2-)
unnamed: C78.1, U15.2 (VS+)
unnamed: C79.1, U15.6 (VS-)
V5: C63.1, L6.1, R43.2, U11.8 (V+)
VBUS: C2.1, C9.1, D7.1 (A1), D11.2 (A), J1.A4 (VBUS), J1.A9 (VBUS), J1.B4 (VBUS), J1.B9 (VBUS), L3.2, L4.2, L6.2, R1.1
VCC: C4.1, C5.1, C7.1, C8.1, C10.1, C11.1, C12.1, C13.1, C14.1, C15.1, C16.1, C17.1, C18.1, C19.1, C20.1, C21.1, C22.1, C23.1, C24.1, C25.1, C26.1, C27.1, C28.1, C29.1, C30.+, C33.1, C34.1, C35.1, C36.1, C37.1, C38.1, C39.1, C53.1, C54.1, C55.1, C56.1, C57.1, C58.1, C59.1, C60.1, C61.1, C62.1, C64.1, C66.1, L1.1, L2.1, LCD1.5 (LEDA), LCD1.7 (VDD), R2.1, R3.1, R7.2, R10.1, R12.1, R17.1, R24.1, R34.2, R35.2, R36.2, R51.2, U2.A1 (VCC), U2.A16 (VCC), U2.D5 (VCCIO0), U2.D12 (VCCIO0), U2.E4 (VCCIO5), U2.E13 (VCCIO1), U2.G7 (VCC), U2.G8 (VCCIO0), U2.G9 (VCCIO0), U2.G10 (VCC), U2.H7 (VCCIO4), U2.H10 (VCCIO1), U2.J7 (VCCIO4), U2.J10 (VCCIO1), U2.K7 (VCC), U2.K8 (VCCIO2), U2.K9 (VCCIO2), U2.K10 (VCC), U2.M4 (VCCIO3), U2.M13 (VCCIO1), U2.N5 (VCCIO2), U2.N12 (VCCIO2), U2.T1 (VCC), U2.T16 (VCC), U3.7 (VCC), U3.8 (VCC), U3.44 (VCC), U3.57 (VCC), U3.70 (VCC), U3.71 (VCC), U3.90 (VCC), U4.3 (OUT), U5.1 (VDD), U5.3 (VDDQ), U5.9 (VDDQ), U5.15 (VDD), U5.29 (VDD), U5.35 (VDDQ), U5.41 (VDDQ), U5.43 (VDD), U5.49 (VDDQ), U5.55 (VDDQ), U5.75 (VDDQ), U5.81 (VDDQ), U9.20 (VCCIO), U9.31 (VCCIO), U9.42 (VCCIO), U9.50 (VREGIN), U9.56 (VCCIO), U10.6 (VCC), U12.8 (VCC), U13.38 (VCC), U13.39 (VCC), U14.16 (VCC), U15.16 (VCC), X1.1 (EN), X1.4 (VDD), X2.1 (EN), X2.4 (VDD)
VCCESP: C3.+, C31.1, C32.1, C48.1, C51.1, C52.1, J3.4 (VDD), JP1.2 (B), R18.1, R19.1, R20.1, R23.2, R25.2, R26.2, R27.2, R28.2, R29.2, R30.2, R31.2, R32.2, R39.2, U1.3 (OUT), U6.3 (3V3), U7.8 (VCC)

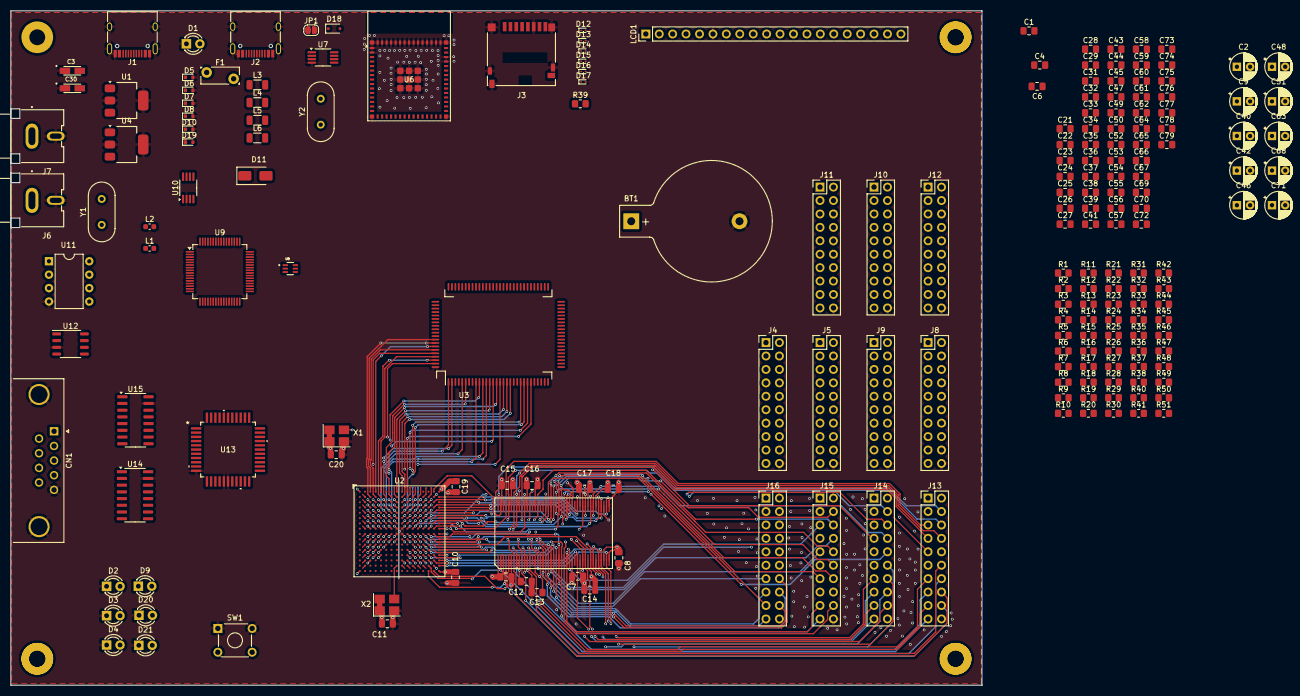
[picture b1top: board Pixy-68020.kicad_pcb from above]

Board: 4 copper layers, 183.7 x 127.6 mm, 198 parts (0 on the bottom side), 290 nets.
